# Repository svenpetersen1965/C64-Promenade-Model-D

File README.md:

# C64-Promenade-Model-D
This is a remake of an  EPROM programmer, originally created by Jason-Ranheim. The project was made in co-operation with <a href="http://c64os.com">C64OS/Greg</a>.

I did the layout, Greg provided the information, has built the prototye and performed the testing (many but not all EPROM Types, that are listed in the <a href="https://github.com/svenpetersen1965/C64-Promenade-Model-D/blob/main/Software/PromenadeC1Man.pdf">manual</a>. A prototype for me was provided by Greg.

So, here are the project files, which I have created, "as is".

Since I did not test the prototype in depth, I am not able to provide support for this project.

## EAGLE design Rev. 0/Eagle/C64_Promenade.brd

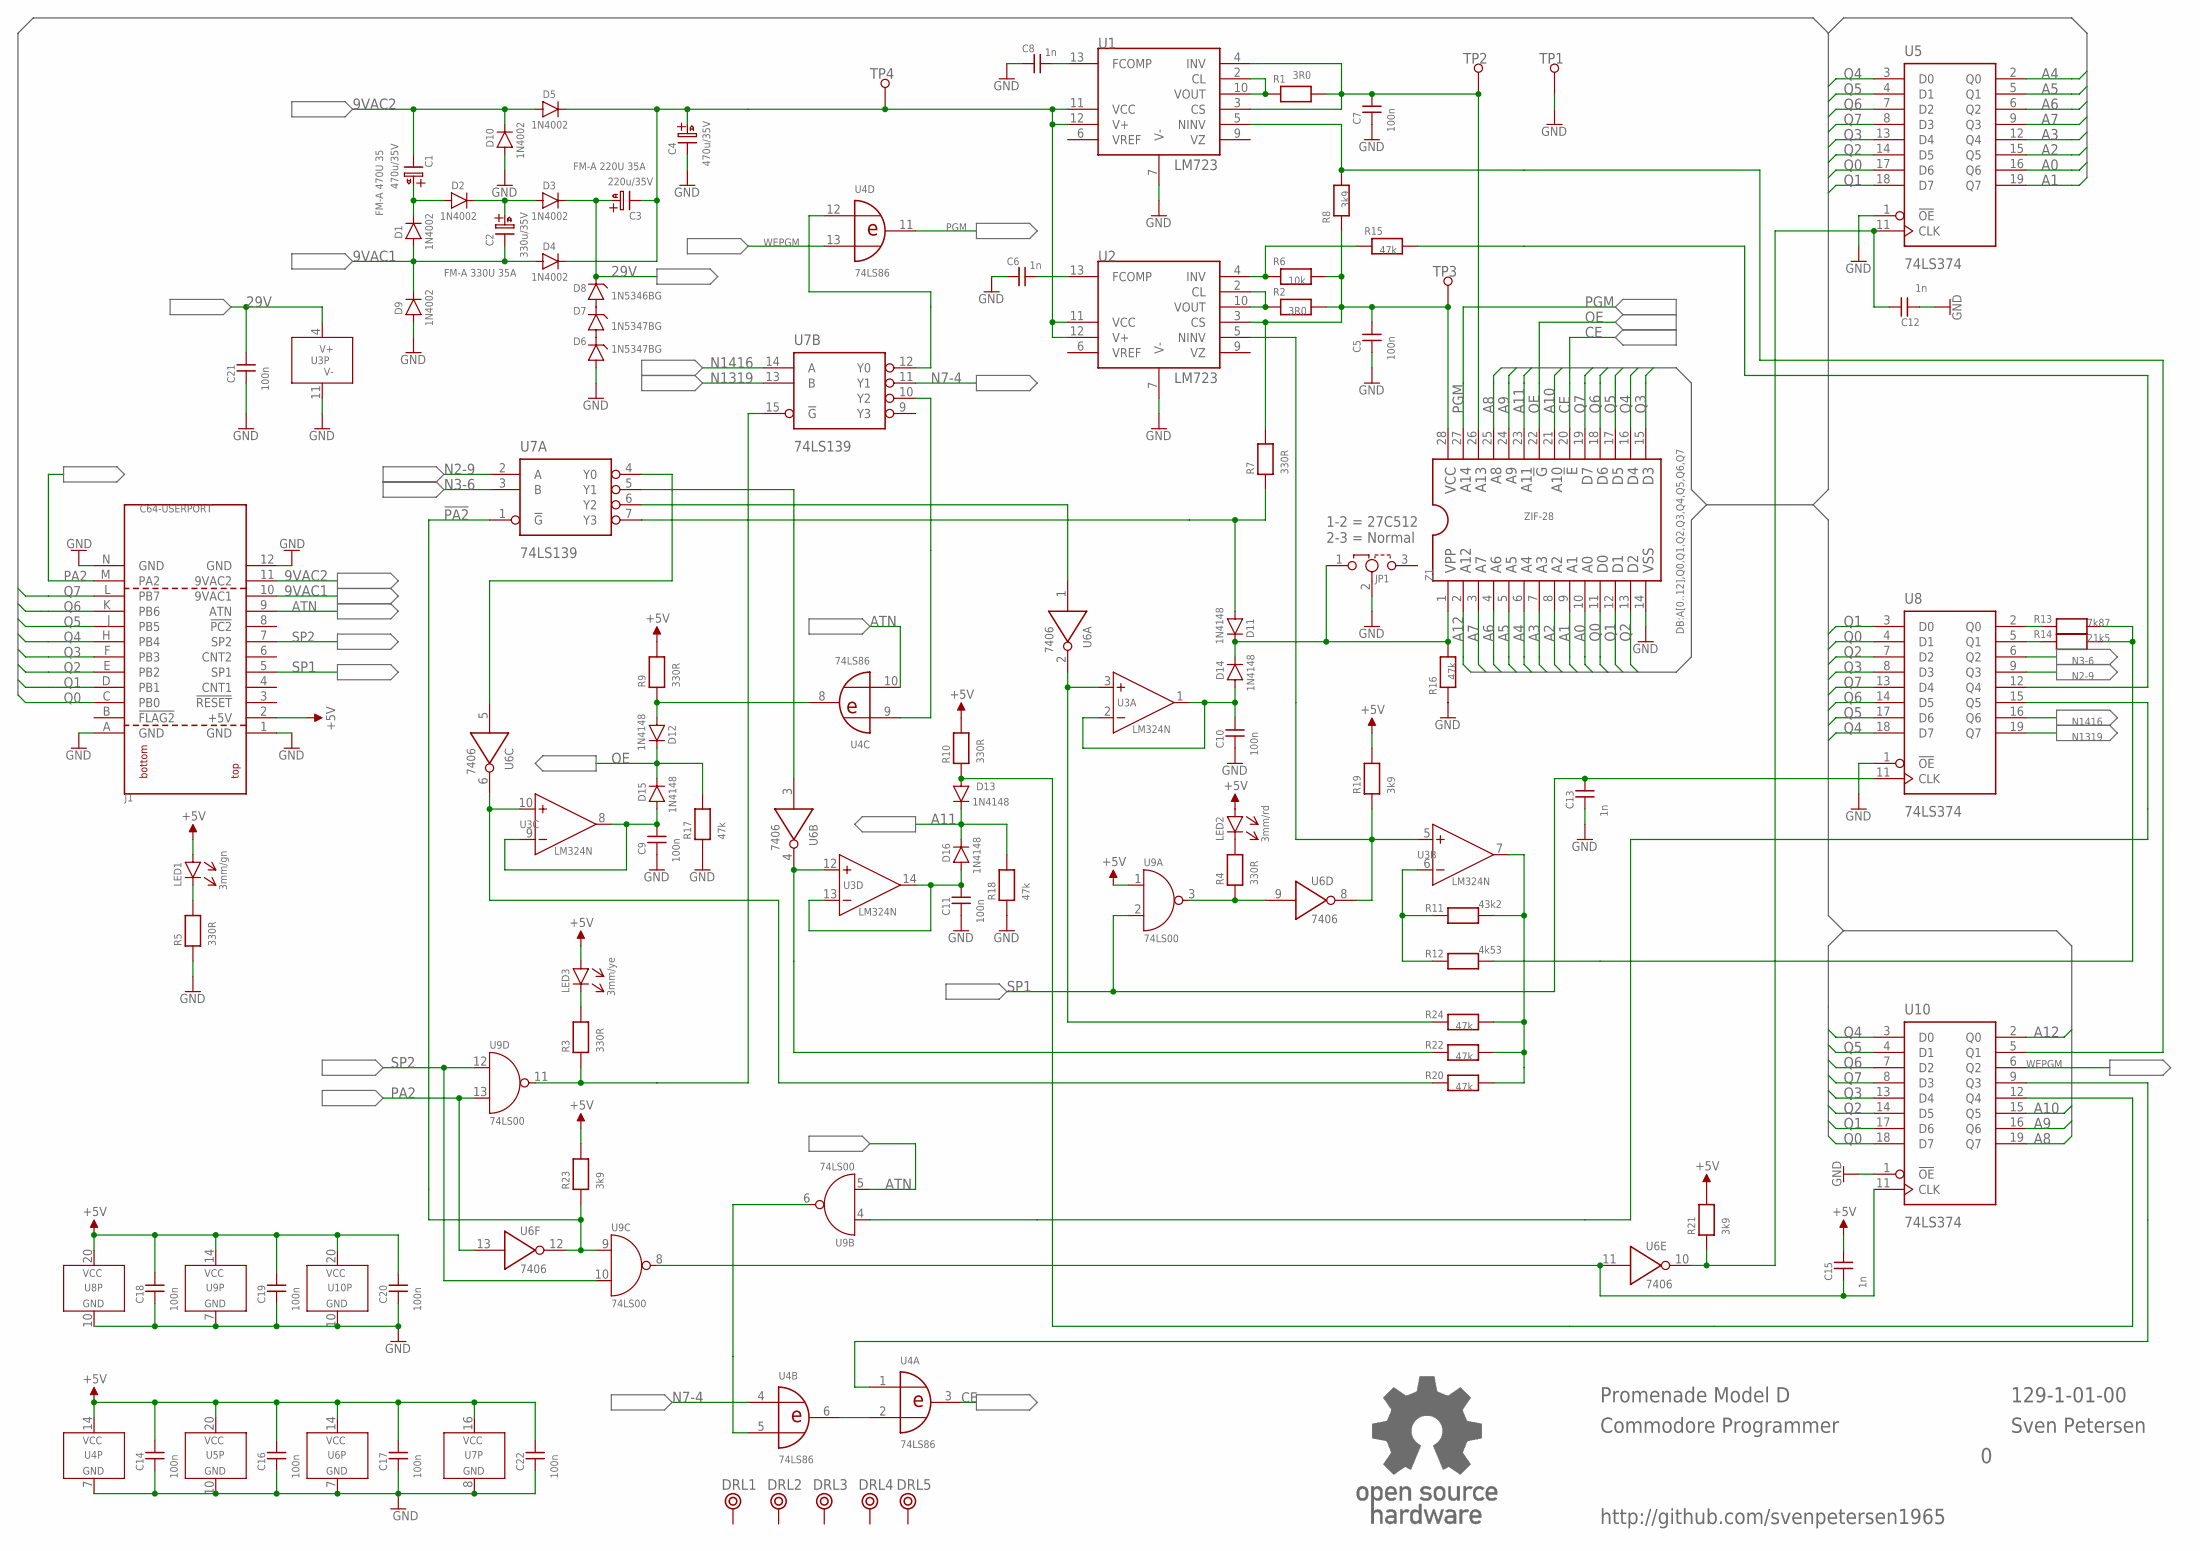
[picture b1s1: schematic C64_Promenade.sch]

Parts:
C1, C4: 470u/35V; C10/5,0
C2: 330u/35V; C10/5,0
C3: 220u/35V; C10/5,0
C5, C7, C9, C10, C11, C14, C16, C17, C18, C19, C20, C21, C22: 100n; C-2,5
C6, C8, C12, C13, C15: 1n; C-2,5
D1, D2, D3, D4, D5, D9, D10: 1N4002; DO-41
D6, D7: 1N5347BG; 017AA
D8: 1N5346BG; 017AA
D11, D12, D13, D14, D15, D16: 1N4148; DO-35
DRL1, DRL2, DRL3, DRL4, DRL5: BOHR3,5
J1: C64-USERPORT; USERPORT
JP1: DJUMPER; 1X03
LED1: 3mm/gn; 3MM
LED2: 3mm/rd; 3MM
LED3: 3mm/ye; 3MM
R1, R2: 3R0; R-10
R3, R4, R5, R7, R9, R10: 330R; R-10
R6: 10k; R-10
R8, R19, R21, R23: 3k9; R-10
R11: 43k2; R-10
R12: 4k53; R-10
R13: 7k87; R-10
R14: 21k5; R-10
R15, R16, R17, R18, R20, R22, R24: 47k; R-10
TP1, TP2, TP3, TP4: 1,3/2,0
U1, U2: LM723; DIL-14
U3: LM324N; DIL-14
U4: 74LS86; DIL-14
U5, U8, U10: 74LS374; DIL-20
U6: 7406; DIL-14
U7: 74LS139; DIL-16
U9: 74LS00; DIL-14
U$80: OPEN_SOURCE_HW; OPENHW
Z1: ZIF-28; ZIF28

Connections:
9VAC1: C2.-, D1.A, D4.A, D9.K, J1.10 (9VAC1)
9VAC2: C1.-, D5.A, D10.K, J1.11 (9VAC2)
29V: C3.+, C21.2, D3.K, D8.K, U3.4 (V+)
!PA2: R23.1, U6.12 (O), U7.1 (!G), U9.9 (I0)
+5V: C14.2, C15.2, C16.2, C17.2, C18.2, C19.2, C20.2, C22.2, J1.2 (+5V), LED1.A, LED2.A, LED3.A, R9.2, R10.2, R19.2, R21.2, R23.2, U4.14 (VCC), U5.20 (VCC), U6.14 (VCC), U7.16 (VCC), U8.20 (VCC), U9.1 (I0), U9.14 (VCC), U10.20 (VCC)
A0: U5.16 (Q6), Z1.10
A1: U5.19 (Q7), Z1.9
A2: U5.15 (Q5), Z1.8
A3: U5.12 (Q4), Z1.7
A4: U5.2 (Q0), Z1.6
A5: U5.5 (Q1), Z1.5
A6: U5.6 (Q2), Z1.4
A7: U5.9 (Q3), Z1.3
A8: U10.19 (Q7), Z1.25
A9: U10.16 (Q6), Z1.24
A10: U10.15 (Q5), Z1.21
A11: D13.K, D16.K, R18.2, Z1.23
A12: U10.2 (Q0), Z1.2
ATN: J1.9 (ATN), U4.10 (I1), U9.5 (I1)
CE: U4.3 (O), Z1.20
GND: C4.-, C5.1, C6.1, C7.1, C8.1, C9.1, C10.1, C11.1, C12.1, C13.1, C14.1, C16.1, C17.1, C18.1, C19.1, C20.1, C21.1, C22.1, D6.A, D9.A, D10.A, J1.1 (GND), J1.12 (GND), J1.A (GND), J1.N (GND), JP1.2, R5.1, R16.2, R17.1, R18.1, TP1.1, U1.7 (V-), U2.7 (V-), U3.11 (V-), U4.7 (GND), U5.1 (!OE), U5.10 (GND), U6.7 (GND), U7.8 (GND), U8.1 (!OE), U8.10 (GND), U9.7 (GND), U10.1 (!OE), U10.10 (GND), Z1.14
N2-9: U7.2 (A), U8.9 (Q3)
N3-6: U7.3 (B), U8.6 (Q2)
N7-4: U4.4 (I0), U7.11 (Y1)
N1319: U7.13 (B), U8.19 (Q7)
N1416: U7.14 (A), U8.16 (Q6)
unnamed: U6.5 (I), U7.4 (Y0)
unnamed: LED1.C (K), R5.2
unnamed: D7.K, D8.A
unnamed: R3.1, U7.15 (!G), U9.11 (O)
unnamed: LED3.C (K), R3.2
unnamed: U4.2 (I1), U4.6 (O)
unnamed: C9.2, D15.A, U3.8 (O), U3.9 (-)
unnamed: R20.1, U3.10 (+), U6.6 (O)
unnamed: U4.5 (I1), U9.6 (O)
unnamed: D12.A, R9.1, U4.8 (O)
unnamed: U4.9 (I0), U7.10 (Y2)
unnamed: U8.15 (Q5), U9.4 (I0)
unnamed: C11.2, D16.A, U3.13 (-), U3.14 (O)
unnamed: R22.1, U3.12 (+), U6.4 (O)
unnamed: D13.A, R10.1, U10.12 (Q4)
unnamed: D6.K, D7.A
unnamed: U6.3 (I), U7.5 (Y1)
unnamed: C10.2, D14.A, U3.1 (O), U3.2 (-)
unnamed: R24.1, U3.3 (+), U6.2 (O)
unnamed: D11.K, D14.K, JP1.1, R16.1, Z1.1
unnamed: U4.12 (I0), U7.12 (Y0)
unnamed: U6.1 (I), U7.6 (Y2)
unnamed: D11.A, R7.1, U7.7 (Y3)
unnamed: R4.1, U6.9 (I), U9.3 (O)
unnamed: LED2.C (K), R4.2
unnamed: R19.1, U2.5 (NINV), U3.5 (+), U6.8 (O)
unnamed: R11.1, R12.1, U3.6 (-)
unnamed: C15.1, U6.11 (I), U9.8 (O), U10.11 (CLK)
unnamed: R11.2, R20.2, R22.2, R24.2, U3.7 (O)
unnamed: C12.2, R21.1, U5.11 (CLK), U6.10 (O)
unnamed: C1.+, D1.K, D2.A
unnamed: C2.+, D2.K, D3.A
unnamed: C8.2, U1.13 (FCOMP)
unnamed: C3.-, C4.+, D4.K, D5.K, TP4.1, U1.11 (VCC), U1.12 (V+), U2.11 (VCC), U2.12 (V+)
unnamed: R1.2, U1.2 (CL), U1.10 (VOUT)
unnamed: C6.2, U2.13 (FCOMP)
unnamed: R2.2, U2.2 (CL), U2.10 (VOUT)
unnamed: C7.2, R1.1, TP2.1, U1.3 (CS), U1.4 (INV), Z1.26
unnamed: R6.2, R15.2, U2.4 (INV)
unnamed: C5.2, R2.1, R6.1, R7.2, R8.2, TP3.1, U2.3 (CS), Z1.28
unnamed: R8.1, U1.5 (NINV), U10.5 (Q1)
unnamed: R15.1, U8.12 (Q4)
unnamed: R14.2, U8.5 (Q1)
unnamed: R13.2, U8.2 (Q0)
unnamed: R12.2, R13.1, R14.1
unnamed: U4.1 (I0), U10.9 (Q3)
OE: D12.K, D15.K, R17.2, Z1.22
PA2: J1.M (PA2), U6.13 (I), U9.13 (I1)
PGM: U4.11 (O), Z1.27
Q0: J1.C (PB0), U5.17 (D6), U8.4 (D1), U10.18 (D7), Z1.11
Q1: J1.D (PB1), U5.18 (D7), U8.3 (D0), U10.17 (D6), Z1.12
Q2: J1.E (PB2), U5.14 (D5), U8.7 (D2), U10.14 (D5), Z1.13
Q3: J1.F (PB3), U5.13 (D4), U8.8 (D3), U10.13 (D4), Z1.15
Q4: J1.H (PB4), U5.3 (D0), U8.18 (D7), U10.3 (D0), Z1.16
Q5: J1.J (PB5), U5.4 (D1), U8.17 (D6), U10.4 (D1), Z1.17
Q6: J1.K (PB6), U5.7 (D2), U8.14 (D5), U10.7 (D2), Z1.18
Q7: J1.L (PB7), U5.8 (D3), U8.13 (D4), U10.8 (D3), Z1.19
SP1: C13.2, J1.5 (SP1), U8.11 (CLK), U9.2 (I1)
SP2: J1.7 (SP2), U9.10 (I1), U9.12 (I0)
WEPGM: U4.13 (I1), U10.6 (Q2)

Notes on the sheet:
Promenade Model D
Commodore Programmer
Sven Petersen
FM-A 470U 35
FM-A 330U 35A
FM-A 220U 35A
1-2 = 27C512 2-3 = Normal
VCC
VPP
A14
A13
A11
A10
VSS
A12
129-1-01-00
http://github.com/svenpetersen1965

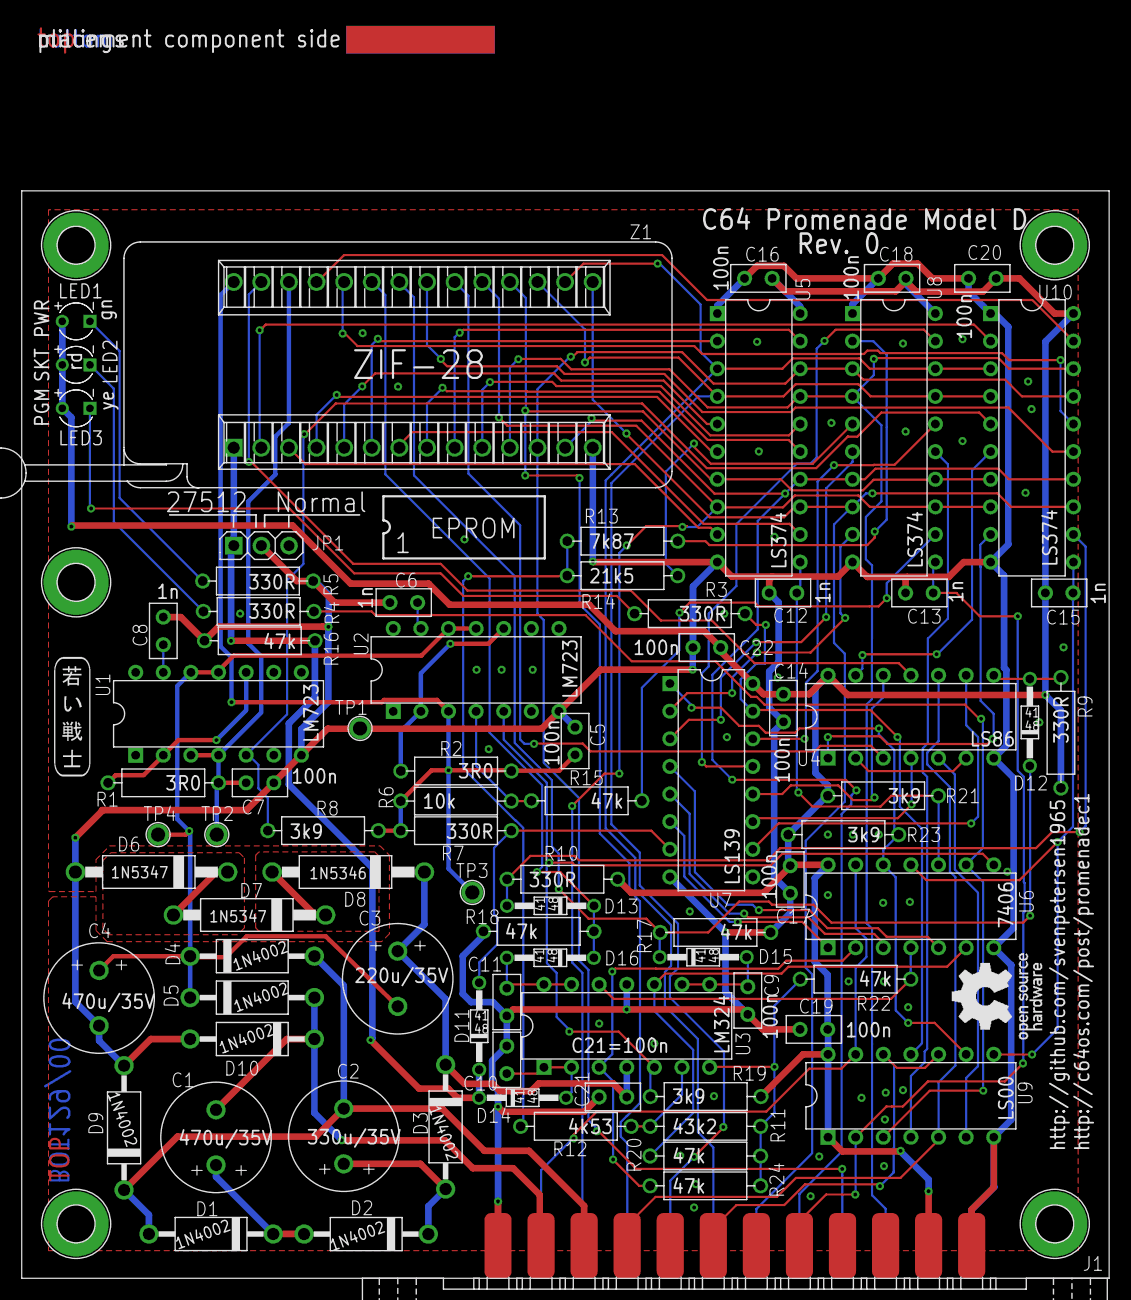
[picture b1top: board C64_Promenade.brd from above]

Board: 2 copper layers, 100.0 x 115.6 mm, 91 parts (0 on the bottom side), 86 nets.

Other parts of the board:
U$70: PCB-TITLE/
U$71: 2LAYER
U$81: SVEN_TAG

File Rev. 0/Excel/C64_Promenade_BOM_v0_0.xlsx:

C64 Promenade Rev. 0
Bill of Material Rev. 0.0
Pos. | Qty | Value | Footprint | Ref.-No. | Comment
1 | 1 | 129-2-01-00 | 2 Layer | PCB Rev. 0 | 2 layer, Cu 35µ, HASL, 100 x 100, 1.6mm FR4
2 | 2 | 470u/35V | C10/5,0 | C1, C4 | El. cap., diam. 10mm, pitch 5,0mm, 105°C
3 | 1 | 330u/35V | C10/5,0 | C2 | El. cap., diam. 10mm, pitch 5,0mm, 105°C
4 | 1 | 220u/35V | C10/5,0 | C3 | El. cap., diam. 10mm, pitch 5,0mm, 105°C
5 | 13 | 100n | C-2,5 | C5, C7, C9, C10, C11, C14, C16, C17, C18, C19, C20, C21, C22 | cer. cap, 2.5mm pitch
6 | 5 | 1n | C-2,5 | C6, C8, C12, C13, C15 | cer. cap, 2.5mm pitch
7 | 7 | 1N4002 | DO-41 | D1, D2, D3, D4, D5, D9, D10
8 | 6 | 1N4148 | DO-35 | D11, D12, D13, D14, D15, D16
9 | 2 | 1N5347BG | 017AA | D6, D7 | On-Semi, Zener 10V, 5W
10 | 1 | 1N5346BG | 017AA | D8 | On-Semi, Zener 9.1V, 5W
11 | 1 | 2x12, 3,96mm | USERPORT | J1 | Edge connector for C64 User Port
12 | 1 | pinheader 3p, 2.54mm | 1X03 | JP1 | plus 1 jumper
13 | 1 | 3mm/gn | 3MM | LED1 | led 3mm, green
14 | 1 | 3mm/rd | 3mm | LED2 | led 3mm, red
15 | 1 | 3mm/ye | 3MM | LED3 | led 3mm, yellow
16 | 2 | 3R0 | R-10 | R1, R2 | Resistor 1/4W, 5%
17 | 1 | 43k2 | R-10 | R11 | Resistor 1/4W, 1%
18 | 1 | 4k53 | R-10 | R12 | Resistor 1/4W, 1%
19 | 1 | 7k87 | R-10 | R13 | Resistor 1/4W, 1%
20 | 1 | 21k5 | R-10 | R14 | Resistor 1/4W, 1%
21 | 7 | 47k | R-10 | R15, R16, R17, R18, R20, R22, R24 | Resistor 1/4W, 5%
22 | 6 | 330R | R-10 | R3, R4, R5, R7, R9, R10 | Resistor 1/4W, 5%
23 | 1 | 10k | R-10 | R6 | Resistor 1/4W, 5%
24 | 4 | 3k9 | R-10 | R8, R19, R21, R23 | Resistor 1/4W, 5%
25 | 2 | LM723 | DIL-14 | U1, U2
26 | 1 | LM324N | DIL-14 | U3
27 | 1 | SN74LS86 | DIL-14 | U4
28 | 3 | SN74LS374 | DIL-20 | U5, U8, U10
29 | 1 | SN7406N | DIL-14 | U6
30 | 1 | SN74LS139 | DIL-16 | U7
31 | 1 | SN74LS00 | DIL-14 | U9
32 | 1 | ZIF-28 | ZIF28 | Z1 | ZIF socket, 28p
